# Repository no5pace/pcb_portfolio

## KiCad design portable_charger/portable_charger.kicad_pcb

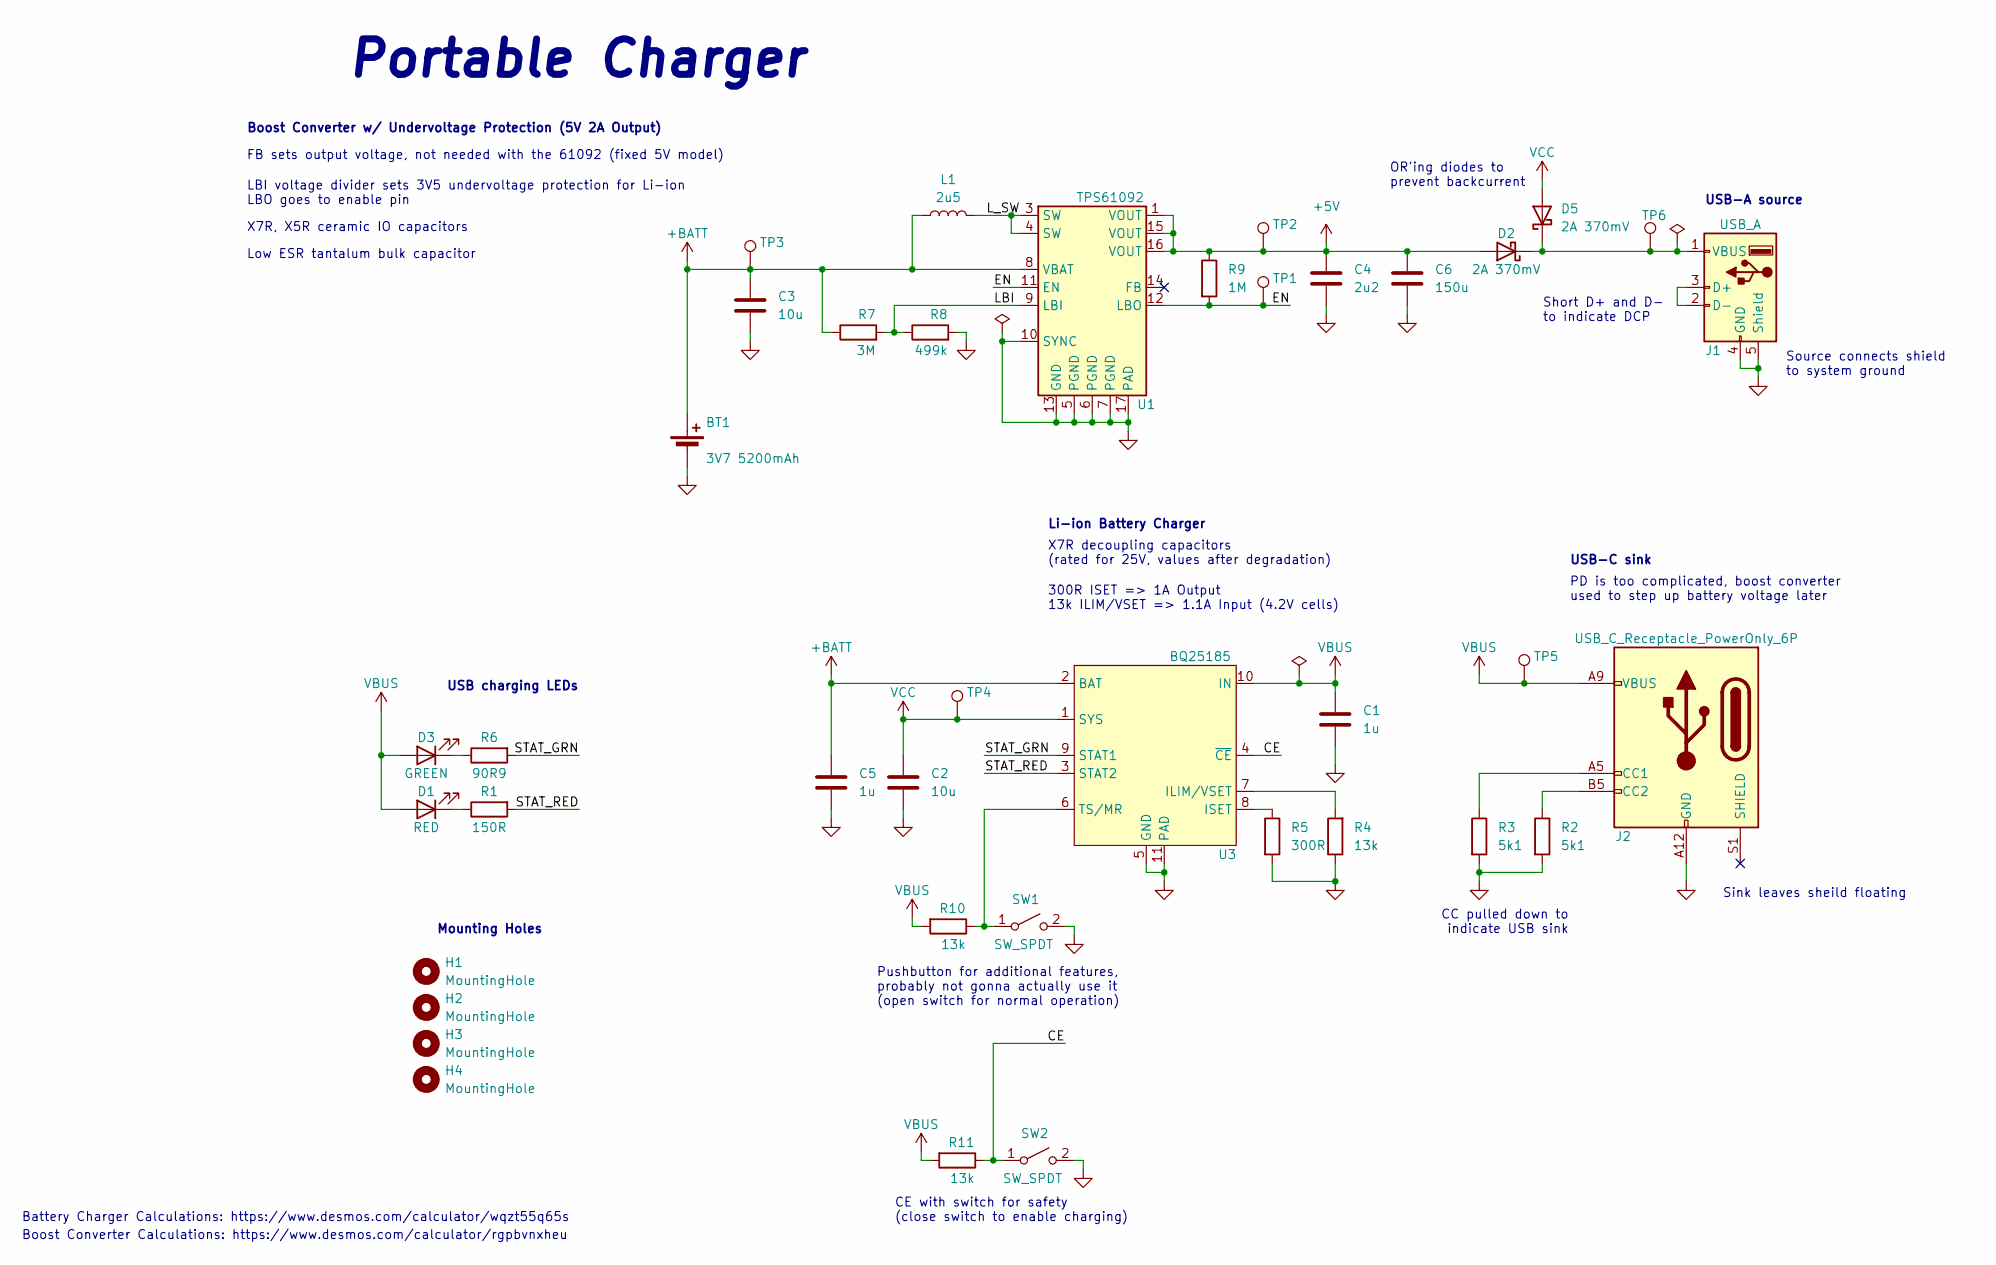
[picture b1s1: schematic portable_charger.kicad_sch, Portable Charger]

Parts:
BT1: 3V7 5200mAh; PinHeader_1x02_P2.54mm_Vertical
C1, C5: 1u; C_0805_2012Metric
C2, C3: 10u; C_0805_2012Metric
C4: 2u2; C_1206_3216Metric
C6: 150u; CP_EIA-7361-38_AVX-V
D1: RED; LED_0603_1608Metric
D2, D5: 2A 370mV; D_SOD-128
D3: GREEN; LED_0603_1608Metric
H1, H2, H3, H4: MountingHole; MountingHole_2.2mm_M2_Pad_Via
J1: USB_A; USB_A_Molex_67643_Horizontal
J2: USB_C_Receptacle_PowerOnly_6P; USB_C_Receptacle_GCT_USB4125-xx-x_6P_TopMnt_Horizontal
L1: 2u5; L_Wuerth_WE-PD-Typ-LS
R1: 150R; R_0805_2012Metric
R2, R3: 5k1; R_0805_2012Metric
R4, R10, R11: 13k; R_0805_2012Metric
R5: 300R; R_0805_2012Metric
R6: 90R9; R_0805_2012Metric
R7: 3M; R_0805_2012Metric
R8: 499k; R_0805_2012Metric
R9: 1M; R_0805_2012Metric
SW1: SW_SPDT; SW_SPST_TL3305A
SW2: SW_SPDT; SW_CuK_OS102011MA1QN1_SPDT_Angled
TP1: En; TestPoint_Pad_D1.0mm
TP2: 5V; TestPoint_Pad_D1.0mm
TP3: +Batt; TestPoint_Pad_D1.0mm
TP4: Sys; TestPoint_Pad_D1.0mm
TP5: USB_C; TestPoint_Pad_D1.0mm
TP6: USB-A; TestPoint_Pad_D1.0mm
U1: TPS61092; Texas_S-PVQFN-N16_EP2.7x2.7mm_ThermalVias
U3: BQ25185; BQ25185DLHR

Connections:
+5V: C4.1, C6.1, D2.2 (A), R9.1, TP2.1, U1.1 (VOUT), U1.15 (VOUT), U1.16 (VOUT)
+BATT: BT1.1 (+), C3.1, C5.1, L1.1, R7.1, TP3.1, U1.8 (VBAT), U3.2 (BAT)
/CE: R11.1, SW2.1 (A), U3.4 (~CE)
/EN: R9.2, TP1.1, U1.11 (EN), U1.12 (LBO)
/LBI: R7.2, R8.1, U1.9 (LBI)
/L_SW: L1.2, U1.3 (SW), U1.4 (SW)
/STAT_GRN: R6.2, U3.9 (STAT1)
/STAT_RED: R1.2, U3.3 (STAT2)
GND: BT1.2 (-), C1.2, C2.2, C3.2, C4.2, C5.2, C6.2, J1.4 (GND), J1.5 (Shield), J2.A12 (GND), J2.B12 (GND), R2.2, R3.2, R4.1, R5.2, R8.2, SW1.2 (B), SW2.2 (B), U1.5 (PGND), U1.6 (PGND), U1.7 (PGND), U1.10 (SYNC), U1.13 (GND), U1.17 (PAD), U3.5 (GND), U3.11 (PAD), U3.12, U3.13
unnamed: D1.1 (K), R1.1
unnamed: D2.1 (K), D5.1 (K), J1.1 (VBUS), TP6.1
unnamed: D3.1 (K), R6.1
unnamed: J1.2 (D-), J1.3 (D+)
unnamed: J2.A5 (CC1), R3.1
unnamed: J2.B5 (CC2), R2.1
unnamed: R10.1, SW1.1 (A), U3.6 (TS/MR)
unnamed: R4.2, U3.7 (ILIM/VSET)
unnamed: R5.1, U3.8 (ISET)
VBUS: C1.1, D1.2 (A), D3.2 (A), J2.A9 (VBUS), J2.B9 (VBUS), R10.2, R11.2, TP5.1, U3.10 (IN)
VCC: C2.1, D5.2 (A), TP4.1, U3.1 (SYS)

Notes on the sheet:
USB-C sink
Li-ion Battery Charger
CC pulled down to indicate USB sink
Low ESR tantalum bulk capacitor
USB charging LEDs
Short D+ and D- to indicate DCP
Boost Converter Calculations: https://www.desmos.com/calculator/rgpbvnxheu
Source connects shield to system ground
USB-A source
X7R, X5R ceramic IO capacitors
Pushbutton for additional features, probably not gonna actually use it (open switch for normal operation)
Mounting Holes
Battery Charger Calculations: https://www.desmos.com/calculator/wqzt55q65s
Sink leaves sheild floating
X7R decoupling capacitors (rated for 25V, values after degradation)
300R ISET => 1A Output 13k ILIM/VSET => 1.1A Input (4.2V cells)
CE with switch for safety (close switch to enable charging)
FB sets output voltage, not needed with the 61092 (fixed 5V model)
Portable Charger
OR'ing diodes to prevent backcurrent
LBI voltage divider sets 3V5 undervoltage protection for Li-ion LBO goes to enable pin
PD is too complicated, boost converter used to step up battery voltage later
Boost Converter w/ Undervoltage Protection (5V 2A Output)

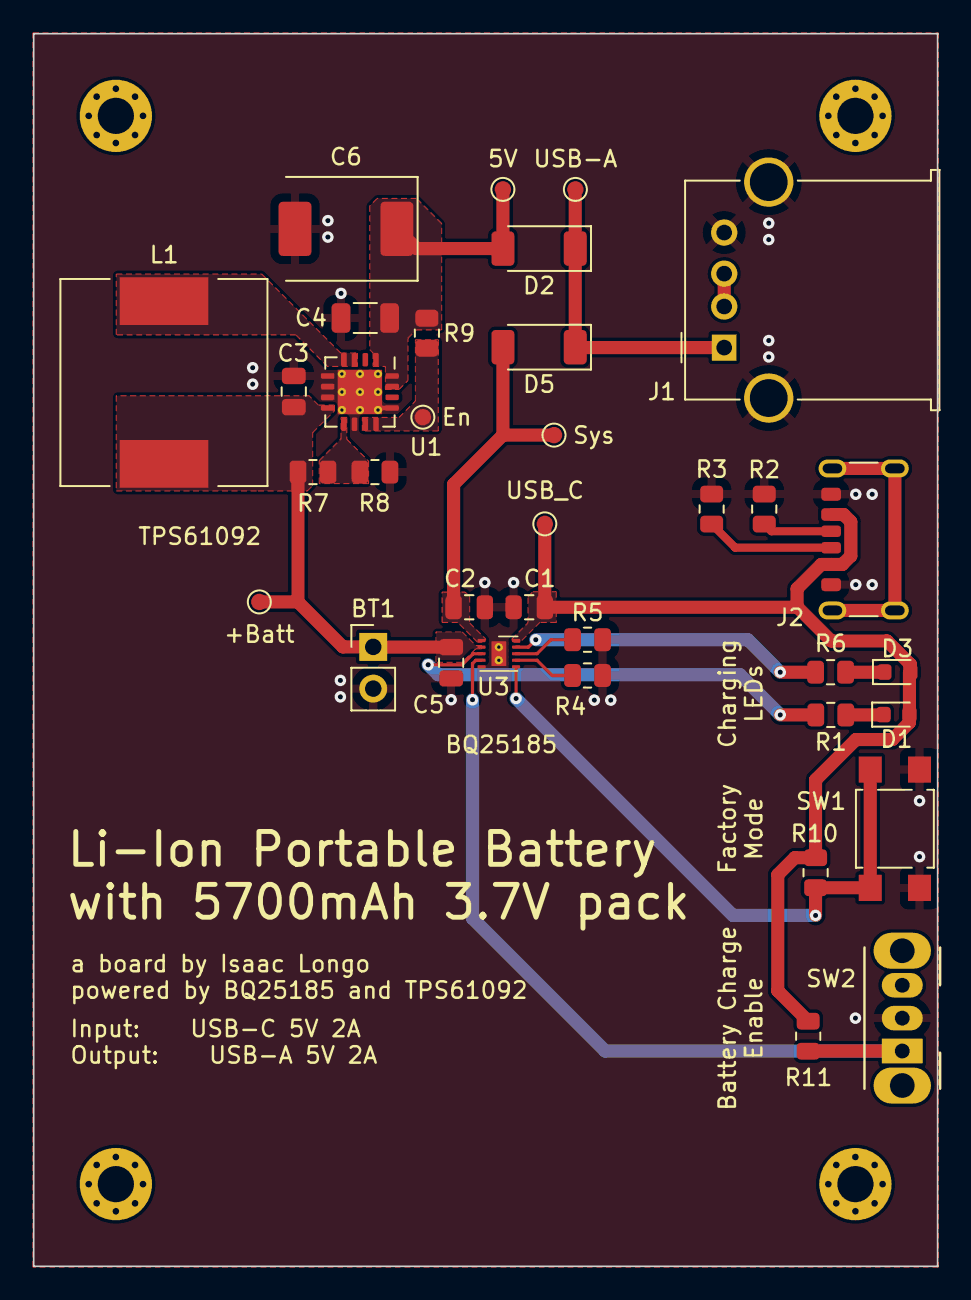
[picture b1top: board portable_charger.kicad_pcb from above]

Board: 2 copper layers, 55.0 x 75.0 mm, 39 parts (0 on the bottom side), 20 nets.

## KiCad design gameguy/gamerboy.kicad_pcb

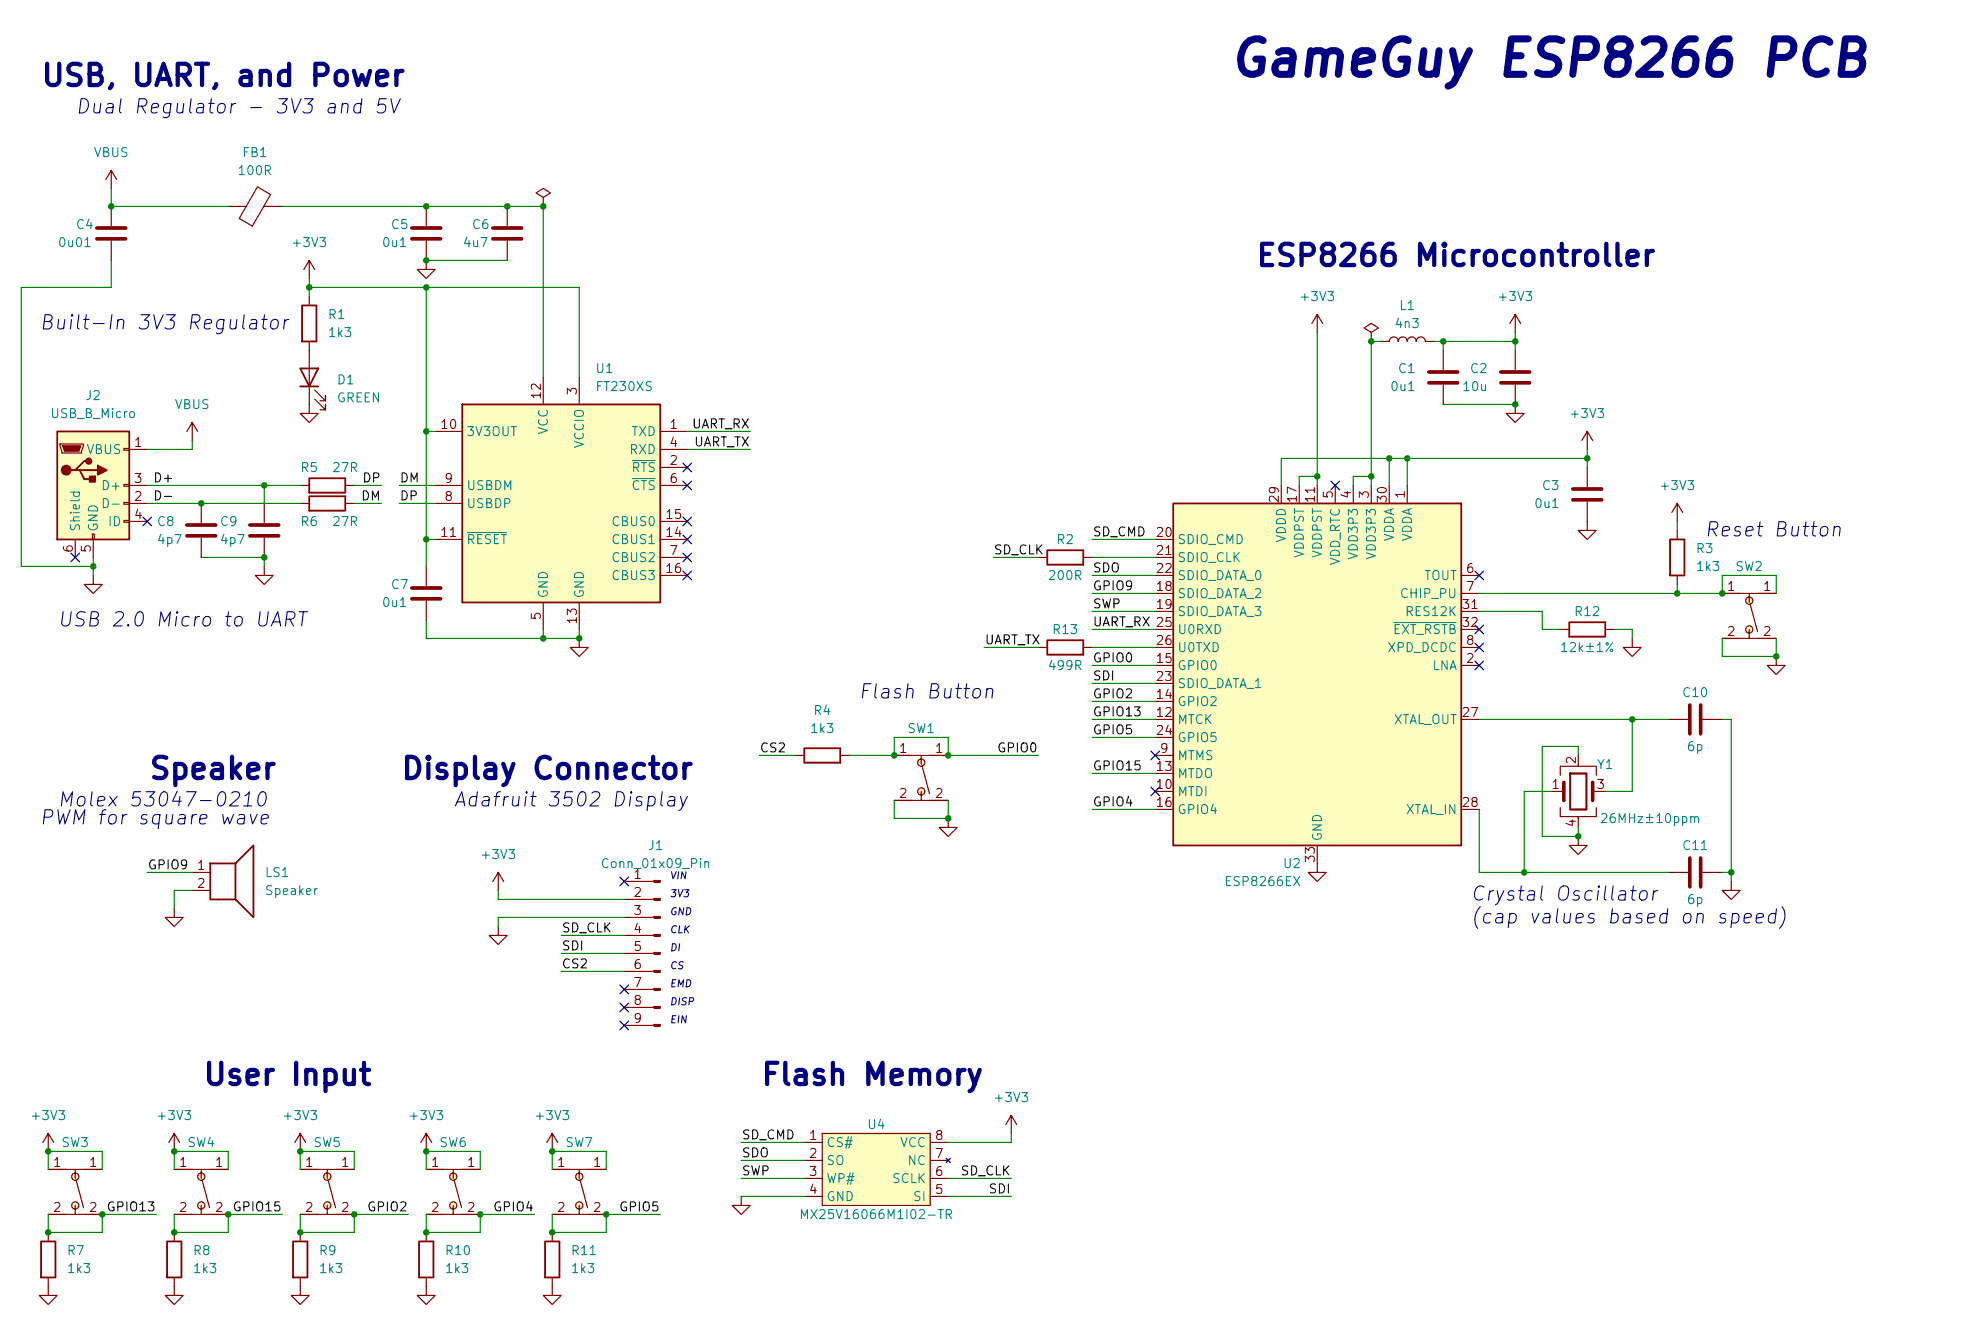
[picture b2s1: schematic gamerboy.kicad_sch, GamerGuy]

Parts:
C1, C3, C5, C7: 0u1; C_0805_2012Metric
C2: 10u; C_0805_2012Metric
C4: 0u01; C_0805_2012Metric
C6: 4u7; C_0805_2012Metric
C8, C9: 4p7; C_0805_2012Metric
C10, C11: 6p; C_0805_2012Metric
D1: GREEN; LED_1206_3216Metric
FB1: 100R; R_0805_2012Metric
J1: Conn_01x09_Pin; PinHeader_1x09_P2.54mm_Vertical
J2: USB_B_Micro; USB_Micro-B_Wuerth_629105150521
L1: 4n3; L_0603_1608Metric
LS1: Speaker; PinHeader_1x02_P2.54mm_Vertical
R1, R3, R4, R7, R8, R9, R10, R11: 1k3; R_0805_2012Metric
R2: 200R; R_0805_2012Metric
R5, R6: 27R; R_0603_1608Metric
R12: 12k±1%; R_0603_1608Metric
R13: 499R; R_0805_2012Metric
SW1, SW2, SW3, SW4, SW5, SW6, SW7: SW_SPST_TL3305A
U1: FT230XS; SSOP-16_3.9x4.9mm_P0.635mm
U2: ESP8266EX; QFN-32-1EP_5x5mm_P0.5mm_EP3.45x3.45mm
U4: MX25V16066M1I02-TR
Y1: 26MHz±10ppm; ABM11-140-26.000MHZ-T3

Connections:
+3V3: C1.1, C2.1, C3.1, C7.1, J1.2, L1.1, R1.1, R3.1, SW3.1, SW4.1, SW5.1, SW6.1, SW7.1, U1.3 (VCCIO), U1.10 (3V3OUT), U1.11 (~RESET), U2.1 (VDDA), U2.11 (VDDPST), U2.17 (VDDPST), U2.29 (VDDD), U2.30 (VDDA), U4.8 (VCC)
/CS2: J1.6, R4.1
/D+: C9.1, J2.3 (D+), R5.2
/D-: C8.1, J2.2 (D-), R6.2
/DM: R6.1, U1.9 (USBDM)
/DP: R5.1, U1.8 (USBDP)
/GPIO0: R4.2, SW1.1, U2.15 (GPIO0)
/GPIO2: R9.1, SW5.2, U2.14 (GPIO2)
/GPIO4: R10.1, SW6.2, U2.16 (GPIO4)
/GPIO5: R11.1, SW7.2, U2.24 (GPIO5)
/GPIO9: LS1.1, U2.18 (SDIO_DATA_2)
/GPIO13: R7.1, SW3.2, U2.12 (MTCK)
/GPIO15: R8.1, SW4.2, U2.13 (MTDO)
/SDI: J1.5, U2.23 (SDIO_DATA_1), U4.5 (SI)
/SDO: U2.22 (SDIO_DATA_0), U4.2 (SO)
/SD_CLK: J1.4, R2.1, U4.6 (SCLK)
/SD_CMD: U2.20 (SDIO_CMD), U4.1 (CS#)
/SWP: U2.19 (SDIO_DATA_3), U4.3 (WP#)
/UART_RX: U1.1 (TXD), U2.25 (U0RXD)
/UART_TX: R13.1, U1.4 (RXD)
GND: C1.2, C2.2, C3.2, C4.2, C5.2, C6.2, C7.2, C8.2, C9.2, C10.2, C11.2, D1.1 (K), J1.3, J2.5 (GND), LS1.2, R7.2, R8.2, R9.2, R10.2, R11.2, R12.1, SW1.2, SW2.2, U1.5 (GND), U1.13 (GND), U2.33 (GND), U4.4 (GND), Y1.2, Y1.4
unnamed: D1.2 (A), R1.2
unnamed: L1.2, U2.3 (VDD3P3), U2.4 (VDD3P3)
unnamed: C5.1, C6.1, FB1.2, U1.12 (VCC)
unnamed: R3.2, SW2.1, U2.7 (CHIP_PU)
unnamed: R12.2, U2.31 (RES12K)
unnamed: R2.2, U2.21 (SDIO_CLK)
unnamed: R13.2, U2.26 (U0TXD)
unnamed: C11.1, U2.28 (XTAL_IN), Y1.1
unnamed: C10.1, U2.27 (XTAL_OUT), Y1.3
VBUS: C4.1, FB1.1, J2.1 (VBUS)

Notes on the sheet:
USB, UART, and Power
EIN
Flash Memory
Molex 53047-0210
GND
3V3
Crystal Oscillator (cap values based on speed)
USB 2.0 Micro to UART
ESP8266 Microcontroller
DISP
Built-In 3V3 Regulator
GameGuy ESP8266 PCB
CLK
Dual Regulator - 3V3 and 5V
Adafruit 3502 Display
EMD
Reset Button
User Input
PWM for square wave
Speaker
Display Connector
Flash Button
VIN

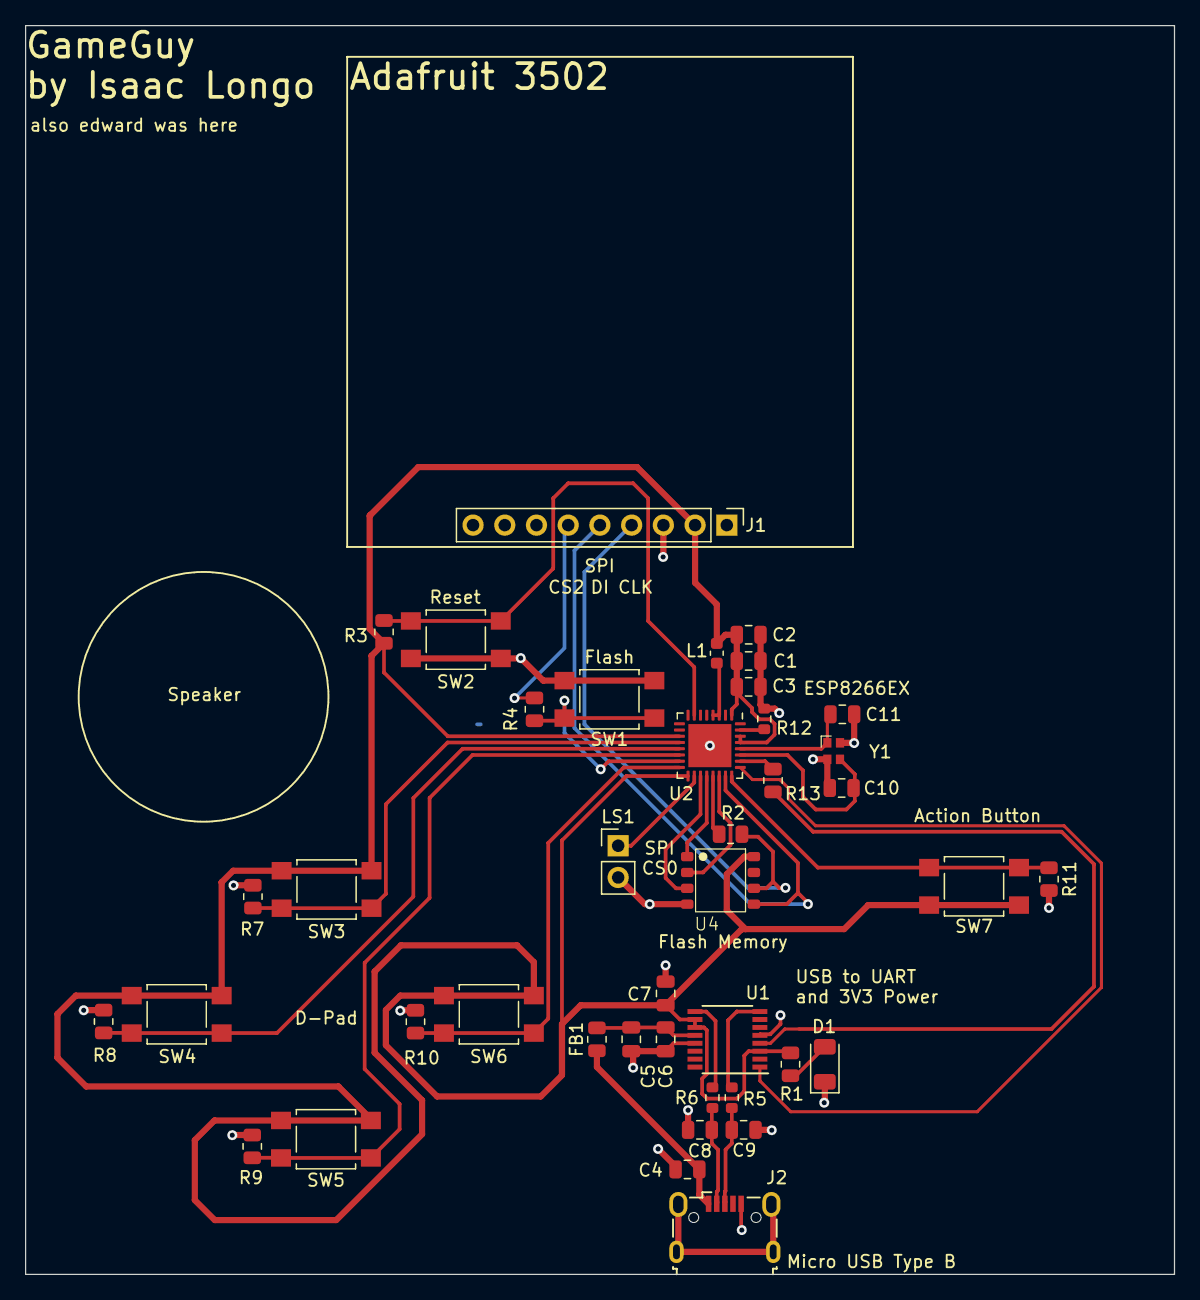
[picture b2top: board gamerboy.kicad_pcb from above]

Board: 2 copper layers, 92.0 x 100.0 mm, 41 parts (0 on the bottom side), 31 nets.
